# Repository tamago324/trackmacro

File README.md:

# trackmacro

> NOTE: KiCad 7 を使用しています

* [monkeypad/pmw3360-breakout](https://github.com/monkeypad/pmw3360-breakout) を使用したトラックボール付きのマクロパッド
* キーボードに載せるお試しで作ったもので、以下の要件を満たすものを作った
    * monkeypad/pmw3360-breakout を使う
        * ピンソケットを使用して、ブレークアウトボードは使い回せるようにする
    * RP2040-Zero を使う
        * PCBの裏にはんだ付けする
            * pmw3360-breakout のセンサの高さが一番高くなるため、裏に配置できた
    * 分割キーボードとして機能させる
    * Chocソケットを使う
        * そのためにトッププレートとボトムプレートをスペーサーとねじで止める構造にする
    * ボールケース
        * GameBall のボールを使ったケースを作成する (38mm)
        * 使い回せるような形状にする
        * ベアリングを使う
* [ファームウェア](https://github.com/tamago324/keyboard-firmwares/tree/master/keyboards/trackmacro)

## 使用している部品

|部品|リンク|備考|
|---|---|---|
|PMW3360ブレークアウトボード|[monkeypad/pmw3360-breakout](https://github.com/monkeypad/pmw3360-breakout)|Booth で購入したら、ピンヘッダーもついていたけど、おそらく[これ](https://www.hirosugi-net.co.jp/shop/c/c12103211/)|
|ピンソケット 8ピン|https://www.hirosugi-net.co.jp/shop/c/c12111211/|FSR-41085-08 / 8.5mmのものを使用する|
|スペーサー M2 5mm|https://www.hirosugi-net.co.jp/shop/c/c10141012/|トッププレートとボトムプレートを止めるために使用する|
|ねじ M2 3mm|https://wilco.jp/products/F/FX-EB.html#page3|トッププレートとボトムプレートを止めるために使用する|
|タッピングネジ M2 8mm|https://wilco.jp/products/F/FPP-N.html|FPP-0000N / ボトムプレートとボールケースを止めるために使用する。JLCPCBのレジンに使えるタッピングネジ|
|RP2040-Zero|||
|ダイオード|||
|chocソケット|||
|TRRSソケット|||

### ボールケース関連

|部品|リンク|備考|
|---|---|---|
|ベアリング|https://amzn.asia/d/8OED4Yl|DDL-520ZZW52 / 内径2mm、外形5mm、幅2.5mm|
|ねじ M2 8mm||なべ小ねじならなんでもOK (頭径3.5mm、高さ1.3)|
|ナット M2||1種のナットを使っている|
|磁石 3x2mm|https://amzn.asia/d/gBrgy0N|ボールケースの上下に瞬間接着剤 (アロンアルフア EXTRA 速効多用途) でつけている|

## 3Dプリント

* JLCPCB の3Dプリントを使う想定
* stl 内の stl ファイルを SLA(Resin) で発注する

## LICENSE

<br />この 作品 は <a rel="license" href="http://creativecommons.org/licenses/by-nc/4.0/">クリエイティブ・コモンズ 表示 - 非営利 4.0 国際 ライセンス</a>の下に提供されています。

> 表示 — あなたは 適切なクレジットを表示し、ライセンスへのリンクを提供し、変更があったらその旨を示さなければなりません。これらは合理的であればどのような方法で行っても構いませんが、許諾者があなたやあなたの利用行為を支持していると示唆するような方法は除きます。
>
> 非営利 — あなたは営利目的でこの資料を利用してはなりません。

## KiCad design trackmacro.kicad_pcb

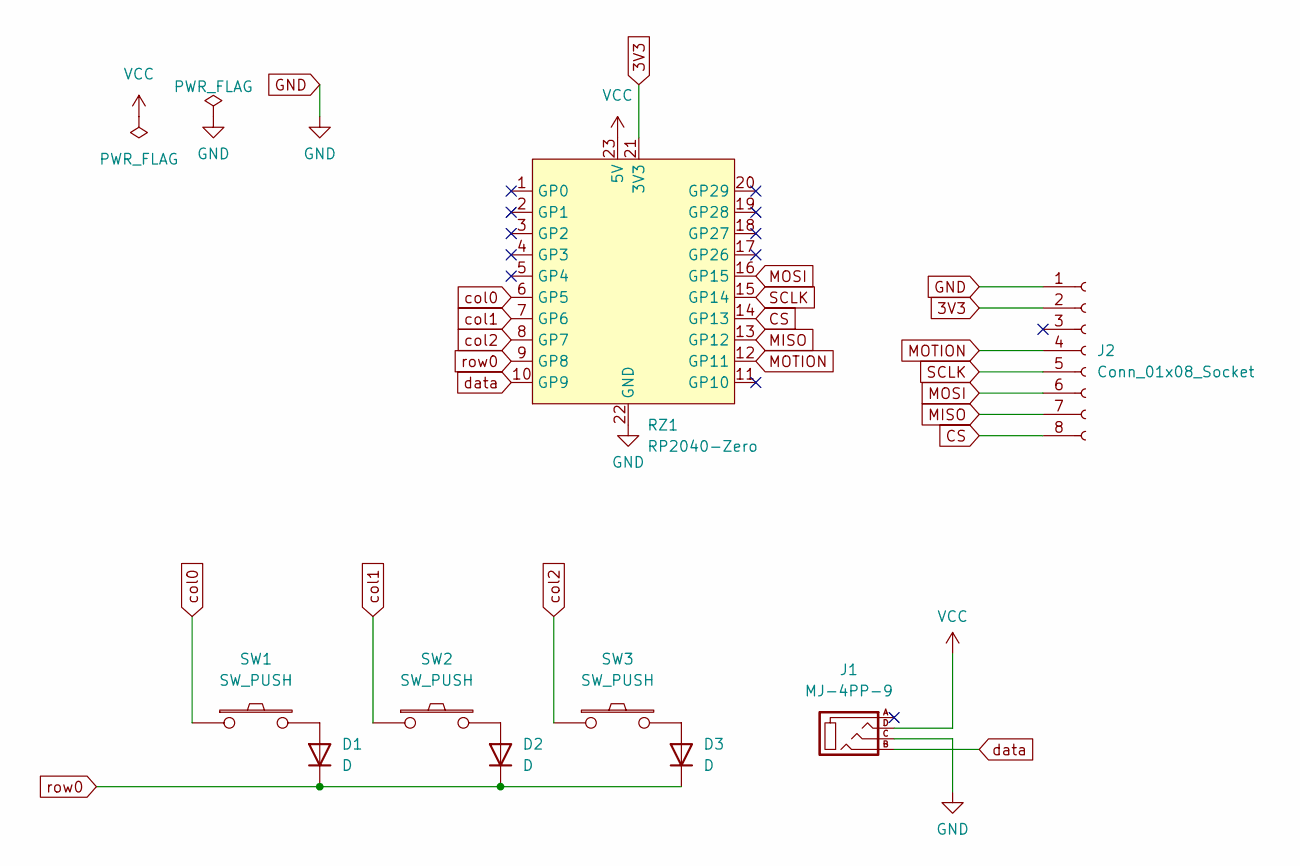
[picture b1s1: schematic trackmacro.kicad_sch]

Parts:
D1, D2, D3: D; D3_SMD
J1: MJ-4PP-9
J2: Conn_01x08_Socket; PinSocket_1x08_P2.54mm
RZ1: RP2040-Zero
SW1, SW2, SW3: SW_PUSH; Kailh_socket_PG1350

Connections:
3V3: J2.2, RZ1.21 (3V3)
CS: J2.8, RZ1.14 (GP13)
GND: J1.C, J2.1, RZ1.22 (GND)
MISO: J2.7, RZ1.13 (GP12)
MOSI: J2.6, RZ1.16 (GP15)
MOTION: J2.4, RZ1.12 (GP11)
unnamed: D1.2 (A), SW1.2
unnamed: D2.2 (A), SW2.2
unnamed: D3.2 (A), SW3.2
SCLK: J2.5, RZ1.15 (GP14)
VCC: J1.D, RZ1.23 (5V)
col0: RZ1.6 (GP5), SW1.1
col1: RZ1.7 (GP6), SW2.1
col2: RZ1.8 (GP7), SW3.1
data: J1.B, RZ1.10 (GP9)
row0: D1.1 (K), D2.1 (K), D3.1 (K), RZ1.9 (GP8)

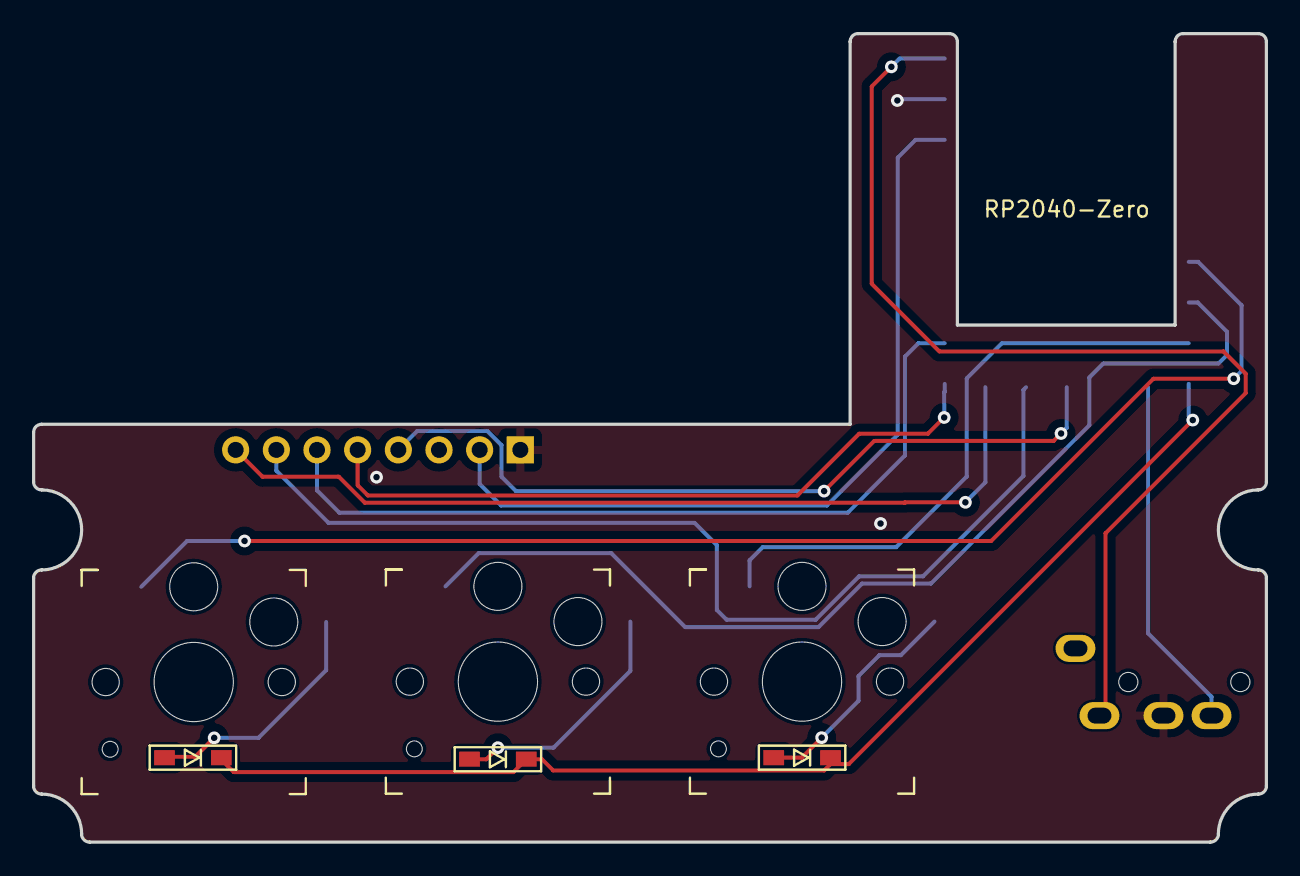
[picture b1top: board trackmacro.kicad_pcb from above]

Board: 2 copper layers, 77.0 x 50.5 mm, 9 parts (0 on the bottom side), 16 nets.

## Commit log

2024-08-29 init
2024-08-29 LICENSE 追加
2024-08-29 写真追加
2024-08-29 NOTE 追加
2024-08-29 ファームウェアのリンクを追加
2024-08-29 GameBall のボール用の説明を追記
2024-10-03 ベアリングの位置は20度で、34,36,38 のボールケースを追加

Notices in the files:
README.md:
LICENSE:
CC BY-NC 4.0
